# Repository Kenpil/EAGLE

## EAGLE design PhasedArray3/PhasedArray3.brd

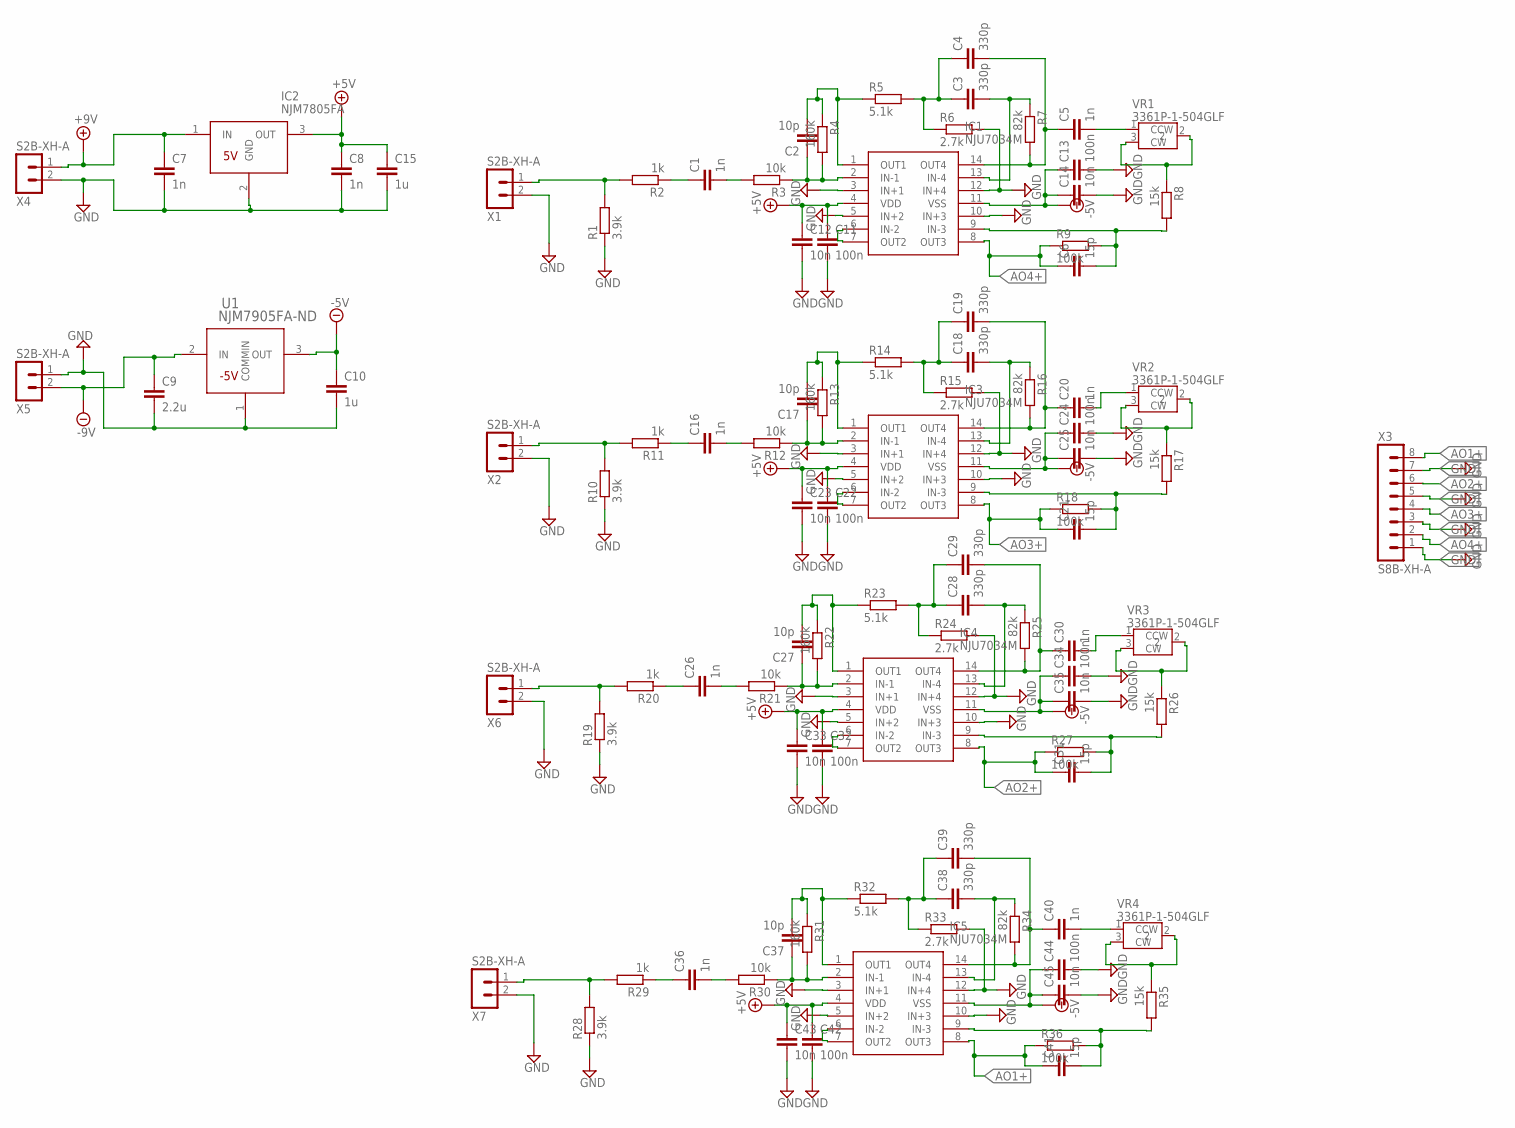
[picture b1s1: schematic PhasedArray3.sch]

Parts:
C1, C5, C7, C8, C16, C20, C26, C30, C36, C40: 1n; C0603K
C2, C17, C27, C37: 10p; C0603K
C3, C4, C18, C19, C28, C29, C38, C39: 330p; C0603K
C6, C21, C31, C41: 15p; C0603K
C9: 2.2u; C0805K
C10, C15: 1u; C0805K
C11, C13, C22, C24, C32, C34, C42, C44: 100n; C0603K
C12, C14, C23, C25, C33, C35, C43, C45: 10n; C0603K
IC1, IC3, IC4, IC5: NJU7034M; SOIC127P680X175-14N
IC2: NJM7805FA; TO254P500X1000X2170-3P
R1, R10, R19, R28: 3.9k; R0603
R2, R11, R20, R29: 1k; R0603
R3, R12, R21, R30: 10k; R0603
R4, R13, R22, R31: 160k; R0603
R5, R14, R23, R32: 5.1k; R0603
R6, R15, R24, R33: 2.7k; R0603
R7, R16, R25, R34: 82k; R0603
R8, R17, R26, R35: 15k; R0603
R9, R18, R27, R36: 100k; R0603
U1: NJM7905FA-ND; NJR-TO-220F-3_NJR
VR1, VR2, VR3, VR4: 3361P-1-504GLF; 3361P1253GLF
X1, X2, X4, X5, X6, X7: S2B-XH-A
X3: S8B-XH-A

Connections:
+5V: C8.1, C11.1, C12.1, C15.1, C22.1, C23.1, C32.1, C33.1, C42.1, C43.1, IC1.4 (VDD), IC2.3 (OUT), IC3.4 (VDD), IC4.4 (VDD), IC5.4 (VDD)
+9V: C7.1, IC2.1 (IN), X4.1
-5V: C10.1, C13.1, C14.1, C24.1, C25.1, C34.1, C35.1, C44.1, C45.1, IC1.11 (VSS), IC3.11 (VSS), IC4.11 (VSS), IC5.11 (VSS), U1.3 (OUT)
-9V: C9.1, U1.2 (IN), X5.2
AO1+: C41.1, IC5.8 (OUT3), R36.1, X3.8
AO2+: C31.1, IC4.8 (OUT3), R27.1, X3.6
AO3+: C21.1, IC3.8 (OUT3), R18.1, X3.4
AO4+: C6.1, IC1.8 (OUT3), R9.1, X3.2
GND: C7.2, C8.2, C9.2, C10.2, C11.2, C12.2, C13.2, C14.2, C15.2, C22.2, C23.2, C24.2, C25.2, C32.2, C33.2, C34.2, C35.2, C42.2, C43.2, C44.2, C45.2, IC1.3 (IN+1), IC1.5 (IN+2), IC1.10 (IN+3), IC1.12 (IN+4), IC2.2 (GND), IC3.3 (IN+1), IC3.5 (IN+2), IC3.10 (IN+3), IC3.12 (IN+4), IC4.3 (IN+1), IC4.5 (IN+2), IC4.10 (IN+3), IC4.12 (IN+4), IC5.3 (IN+1), IC5.5 (IN+2), IC5.10 (IN+3), IC5.12 (IN+4), R1.1, R6.2, R10.1, R15.2, R19.1, R24.2, R28.1, R33.2, U1.1 (COMMIN), X1.2, X2.2, X3.1, X3.3, X3.5, X3.7, X4.2, X5.1, X6.2, X7.2
unnamed: R1.2, R2.2, X1.1
unnamed: C1.1, R2.1
unnamed: C2.2, IC1.1 (OUT1), R4.1, R5.1
unnamed: C1.2, R3.2
unnamed: C2.1, IC1.2 (IN-1), R3.1, R4.2
unnamed: C3.1, C4.1, R5.2, R6.1
unnamed: C4.2, C5.1, IC1.14 (OUT4), R7.2
unnamed: C3.2, IC1.13 (IN-4), R7.1
unnamed: C5.2, VR1.1 (CCW)
unnamed: C6.2, IC1.9 (IN-3), R8.2, R9.2
unnamed: R8.1, VR1.2, VR1.3 (CW)
unnamed: IC1.6 (IN-2), IC1.7 (OUT2)
unnamed: R10.2, R11.2, X2.1
unnamed: C16.1, R11.1
unnamed: C16.2, R12.2
unnamed: C17.1, IC3.2 (IN-1), R12.1, R13.2
unnamed: C17.2, IC3.1 (OUT1), R13.1, R14.1
unnamed: C18.1, C19.1, R14.2, R15.1
unnamed: C18.2, IC3.13 (IN-4), R16.1
unnamed: C19.2, C20.1, IC3.14 (OUT4), R16.2
unnamed: C21.2, IC3.9 (IN-3), R17.2, R18.2
unnamed: C20.2, VR2.1 (CCW)
unnamed: R17.1, VR2.2, VR2.3 (CW)
unnamed: IC3.6 (IN-2), IC3.7 (OUT2)
unnamed: R19.2, R20.2, X6.1
unnamed: C26.1, R20.1
unnamed: C26.2, R21.2
unnamed: C27.1, IC4.2 (IN-1), R21.1, R22.2
unnamed: C27.2, IC4.1 (OUT1), R22.1, R23.1
unnamed: C28.1, C29.1, R23.2, R24.1
unnamed: C28.2, IC4.13 (IN-4), R25.1
unnamed: C29.2, C30.1, IC4.14 (OUT4), R25.2
unnamed: C31.2, IC4.9 (IN-3), R26.2, R27.2
unnamed: C30.2, VR3.1 (CCW)
unnamed: R26.1, VR3.2, VR3.3 (CW)
unnamed: IC4.6 (IN-2), IC4.7 (OUT2)
unnamed: R28.2, R29.2, X7.1
unnamed: C36.1, R29.1
unnamed: C36.2, R30.2
unnamed: C37.1, IC5.2 (IN-1), R30.1, R31.2
unnamed: C37.2, IC5.1 (OUT1), R31.1, R32.1
unnamed: C38.1, C39.1, R32.2, R33.1
unnamed: C38.2, IC5.13 (IN-4), R34.1
unnamed: C39.2, C40.1, IC5.14 (OUT4), R34.2
unnamed: C41.2, IC5.9 (IN-3), R35.2, R36.2
unnamed: C40.2, VR4.1 (CCW)
unnamed: R35.1, VR4.2, VR4.3 (CW)
unnamed: IC5.6 (IN-2), IC5.7 (OUT2)

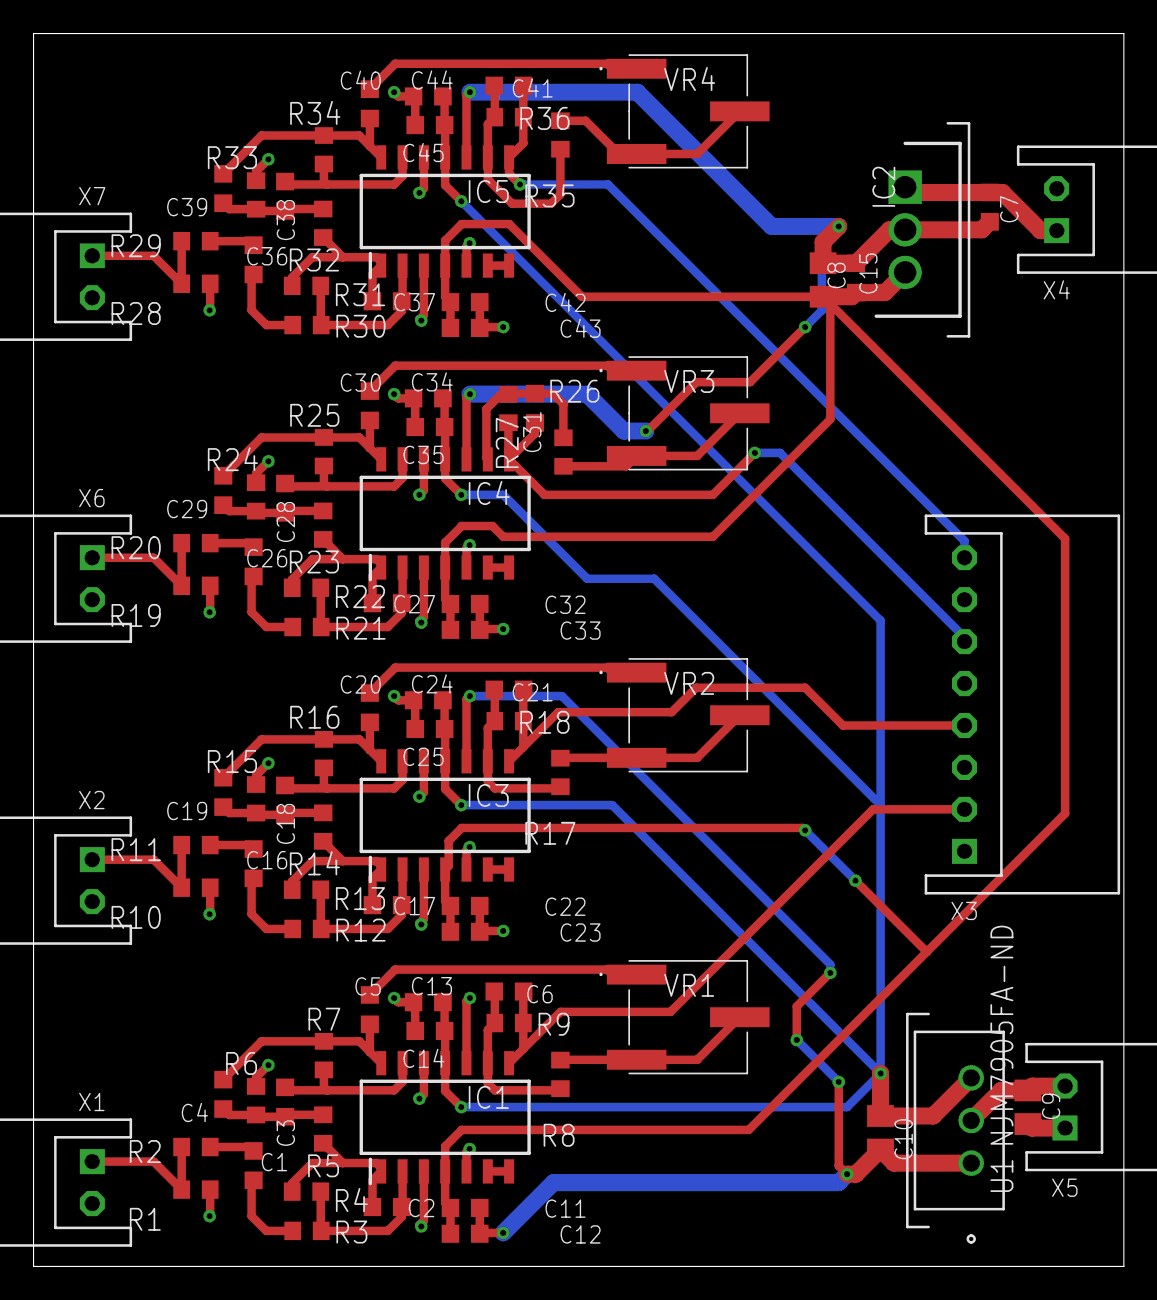
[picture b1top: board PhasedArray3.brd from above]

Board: 2 copper layers, 65.0 x 73.5 mm, 98 parts (0 on the bottom side), 57 nets.

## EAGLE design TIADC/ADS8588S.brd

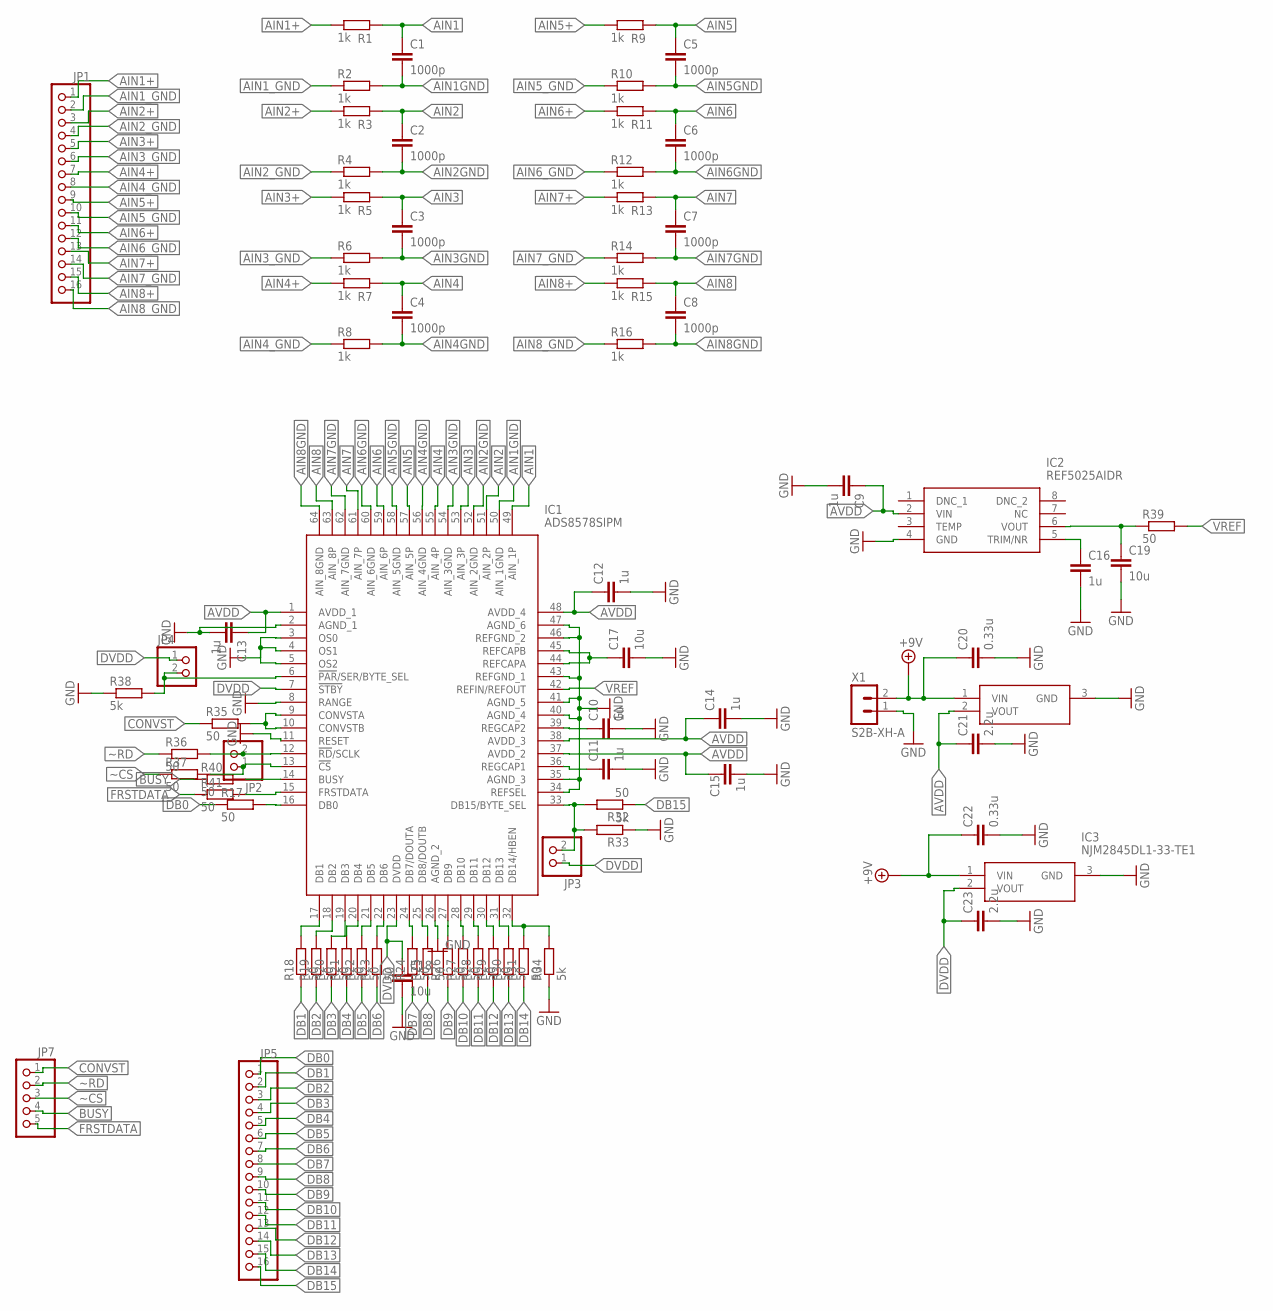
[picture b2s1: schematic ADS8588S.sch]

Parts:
C1, C2, C3, C4, C5, C6, C7, C8: 1000p; C0603K
C9, C10, C11, C12, C13, C14, C15, C16: 1u; C0603K
C17, C18, C19: 10u; C0805K
C20, C22: 0.33u; C0603K
C21, C23: 2.2u; C0805K
IC1: ADS8578SIPM; QFP50P1200X1200X160-64N
IC2: REF5025AIDR; SOIC127P600X175-8N
IC3: NJM2845DL1-33-TE1; TO-252-3-L1
IC5: NJM2845DL1-05-TE1; TO-252-3-L1
JP1, JP5: PINHD-1X16; 1X16
JP2, JP3, JP4: PINHD-1X2; 1X02
JP7: PINHD-1X5; 1X05
R1, R2, R3, R4, R5, R6, R7, R8, R9, R10, R11, R12, R13, R14, R15, R16: 1k; R0603
R17, R18, R19, R20, R21, R22, R23, R24, R25, R26, R27, R28, R29, R30, R31, R32, R35, R36, R37, R39, R40, R41: 50; R0603
R33, R34, R38: 5k; R0603
X1: S2B-XH-A

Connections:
AIN1: C1.1, IC1.49 (AIN_1P), R1.2
AIN1+: JP1.1, R1.1
AIN1GND: C1.2, IC1.50 (AIN_1GND), R2.2
AIN1_GND: JP1.2, R2.1
AIN2: C2.1, IC1.51 (AIN_2P), R3.2
AIN2+: JP1.3, R3.1
AIN2GND: C2.2, IC1.52 (AIN_2GND), R4.2
AIN2_GND: JP1.4, R4.1
AIN3: C3.1, IC1.53 (AIN_3P), R5.2
AIN3+: JP1.5, R5.1
AIN3GND: C3.2, IC1.54 (AIN_3GND), R6.2
AIN3_GND: JP1.6, R6.1
AIN4: C4.1, IC1.55 (AIN_4P), R7.2
AIN4+: JP1.7, R7.1
AIN4GND: C4.2, IC1.56 (AIN_4GND), R8.2
AIN4_GND: JP1.8, R8.1
AIN5: C5.1, IC1.57 (AIN_5P), R9.2
AIN5+: JP1.9, R9.1
AIN5GND: C5.2, IC1.58 (AIN_5GND), R10.2
AIN5_GND: JP1.10, R10.1
AIN6: C6.1, IC1.59 (AIN_6P), R11.2
AIN6+: JP1.11, R11.1
AIN6GND: C6.2, IC1.60 (AIN_6GND), R12.2
AIN6_GND: JP1.12, R12.1
AIN7: C7.1, IC1.61 (AIN_7P), R13.2
AIN7+: JP1.13, R13.1
AIN7GND: C7.2, IC1.62 (AIN_7GND), R14.2
AIN7_GND: JP1.14, R14.1
AIN8: C8.1, IC1.63 (AIN_8P), R15.2
AIN8+: JP1.15, R15.1
AIN8GND: C8.2, IC1.64 (AIN_8GND), R16.2
AIN8_GND: JP1.16, R16.1
AVDD: C9.1, C12.1, C13.1, C14.1, C15.1, C21.1, IC1.1 (AVDD_1), IC1.37 (AVDD_2), IC1.38 (AVDD_3), IC1.48 (AVDD_4), IC2.2 (VIN), IC5.2 (VOUT)
BUSY: JP7.4, R40.1
CONVST: JP7.1, R35.1
DB0: JP5.1, R17.1
DB1: JP5.2, R18.1
DB2: JP5.3, R19.1
DB3: JP5.4, R20.1
DB4: JP5.5, R21.1
DB5: JP5.6, R22.1
DB6: JP5.7, R23.1
DB7: JP5.8, R24.1
DB8: JP5.9, R25.1
DB9: JP5.10, R26.1
DB10: JP5.11, R27.1
DB11: JP5.12, R28.1
DB12: JP5.13, R29.1
DB13: JP5.14, R30.1
DB14: JP5.15, R31.1
DB15: JP5.16, R32.1
DVDD: C18.1, C23.1, IC1.7 (!STBY), IC1.23 (DVDD), IC3.2 (VOUT), JP3.1, JP4.1
DVDD1: C19.1, IC2.6 (VOUT), R39.1
FRSTDATA: JP7.5, R41.1
unnamed: C17.1, IC1.44 (REFCAPA), IC1.45 (REFCAPB)
unnamed: IC1.9 (CONVSTA), IC1.10 (CONVSTB), R35.2
unnamed: C10.1, IC1.39 (REGCAP2)
unnamed: C11.1, IC1.36 (REGCAP1)
unnamed: IC1.17 (DB1), R18.2
unnamed: IC1.18 (DB2), R19.2
unnamed: IC1.19 (DB3), R20.2
unnamed: IC1.20 (DB4), R21.2
unnamed: IC1.21 (DB5), R22.2
unnamed: IC1.22 (DB6), R23.2
unnamed: IC1.24 (DB7/DOUTA), R24.2
unnamed: IC1.25 (DB8/DOUTB), R25.2
unnamed: IC1.27 (DB9), R26.2
unnamed: IC1.28 (DB10), R27.2
unnamed: IC1.29 (DB11), R28.2
unnamed: IC1.30 (DB12), R29.2
unnamed: IC1.31 (DB13), R30.2
unnamed: IC1.32 (DB14/HBEN), R31.2, R34.2
unnamed: IC1.33 (DB15/BYTE_SEL), JP3.2, R32.2, R33.2
unnamed: IC1.16 (DB0), R17.2
unnamed: IC1.6 (!PAR!/SER/BYTE_SEL), JP4.2, R38.2
unnamed: C16.1, IC2.5 (TRIM/NR)
unnamed: IC1.12 (!RD!/SCLK), JP2.2, R36.2
unnamed: IC1.13 (!CS), JP2.1, R37.2
unnamed: IC1.15 (FRSTDATA), R41.2
unnamed: IC1.14 (BUSY), R40.2
VREF: IC1.42 (REFIN/REFOUT), R39.2
~CS: JP7.3, R37.1
~RD: JP7.2, R36.1

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
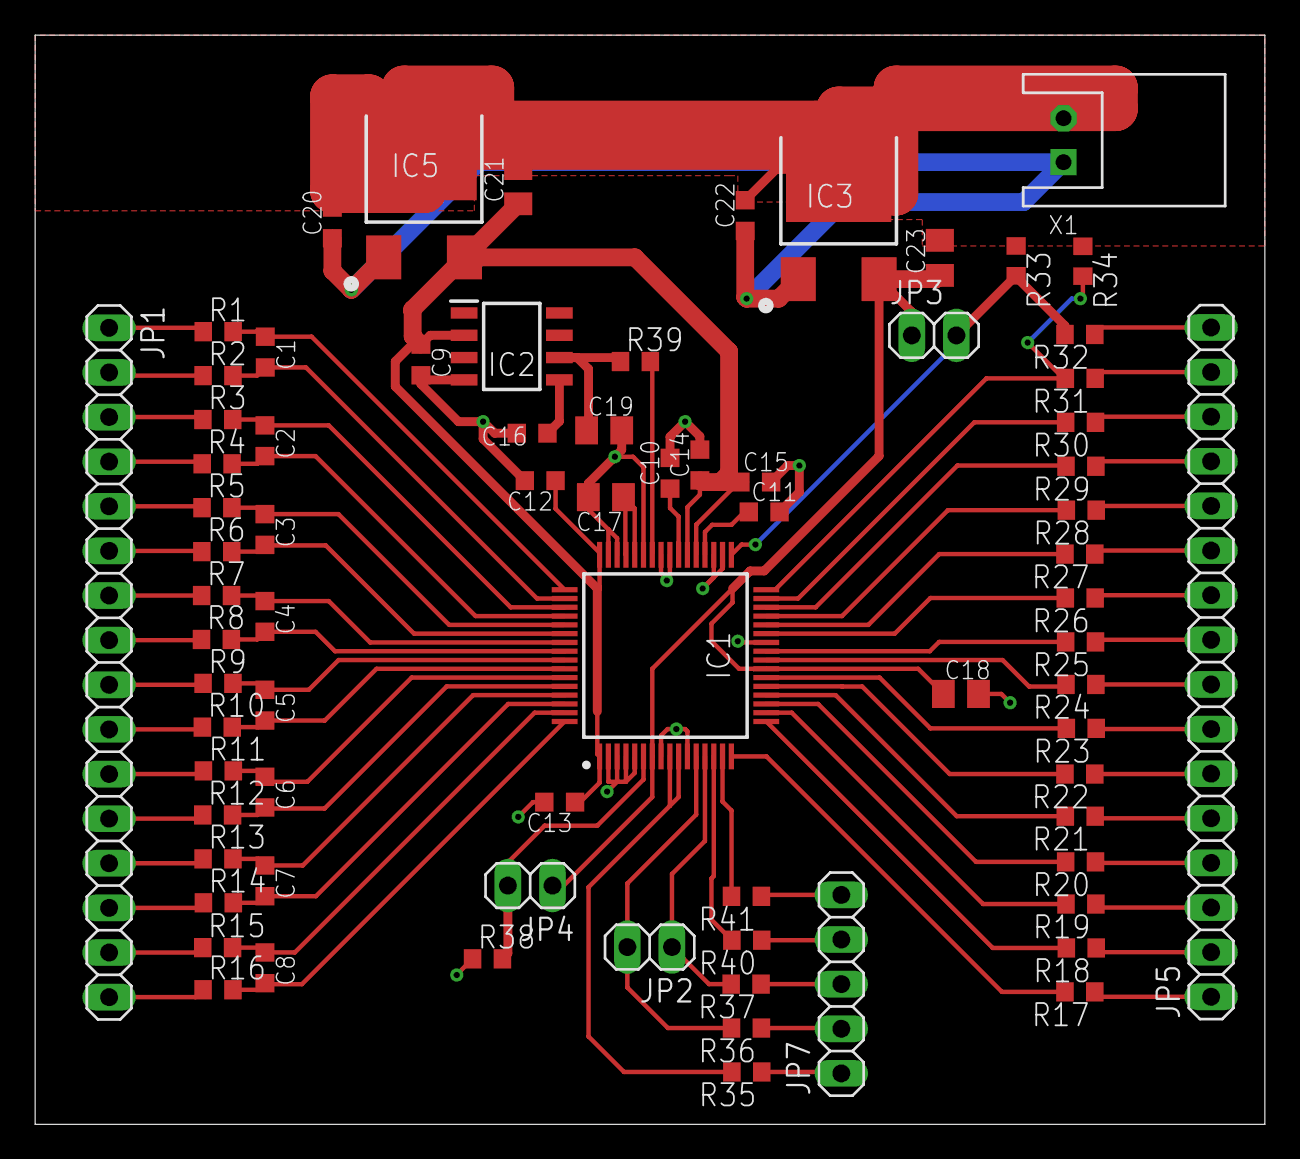
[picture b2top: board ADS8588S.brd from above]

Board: 2 copper layers, 70.0 x 62.0 mm, 75 parts (0 on the bottom side), 85 nets.

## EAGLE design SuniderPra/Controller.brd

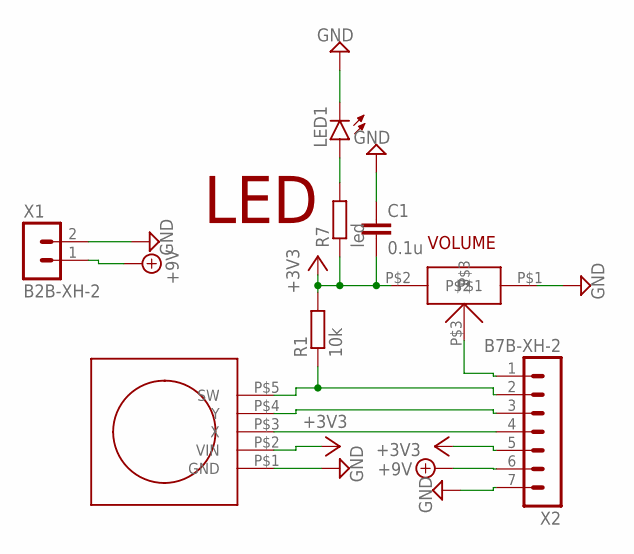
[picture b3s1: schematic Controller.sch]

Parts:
C1: 0.1u; C050-024X044
JOY1: JOY
LED1: LED3MM
POT1: POTENTIOMETER
R1: 10k; 0207/7
R7: led; 0207/7
X1: B2B-XH-2; B2B-XH-A
X2: B7B-XH-2; B7B-XH-A

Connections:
+3V3: C1.2, JOY1.P$2 (VIN), POT1.P$2, R1.2, R7.1, X2.5
+9V: X1.1, X2.6
GND: C1.1, JOY1.P$1 (GND), LED1.K (C), POT1.P$1, X1.2, X2.7
unnamed: JOY1.P$4 (Y), X2.3
unnamed: JOY1.P$5 (SW), R1.1, X2.2
unnamed: POT1.P$3, X2.1
unnamed: JOY1.P$3 (X), X2.4
unnamed: LED1.A, R7.2

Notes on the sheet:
VOLUME
LED

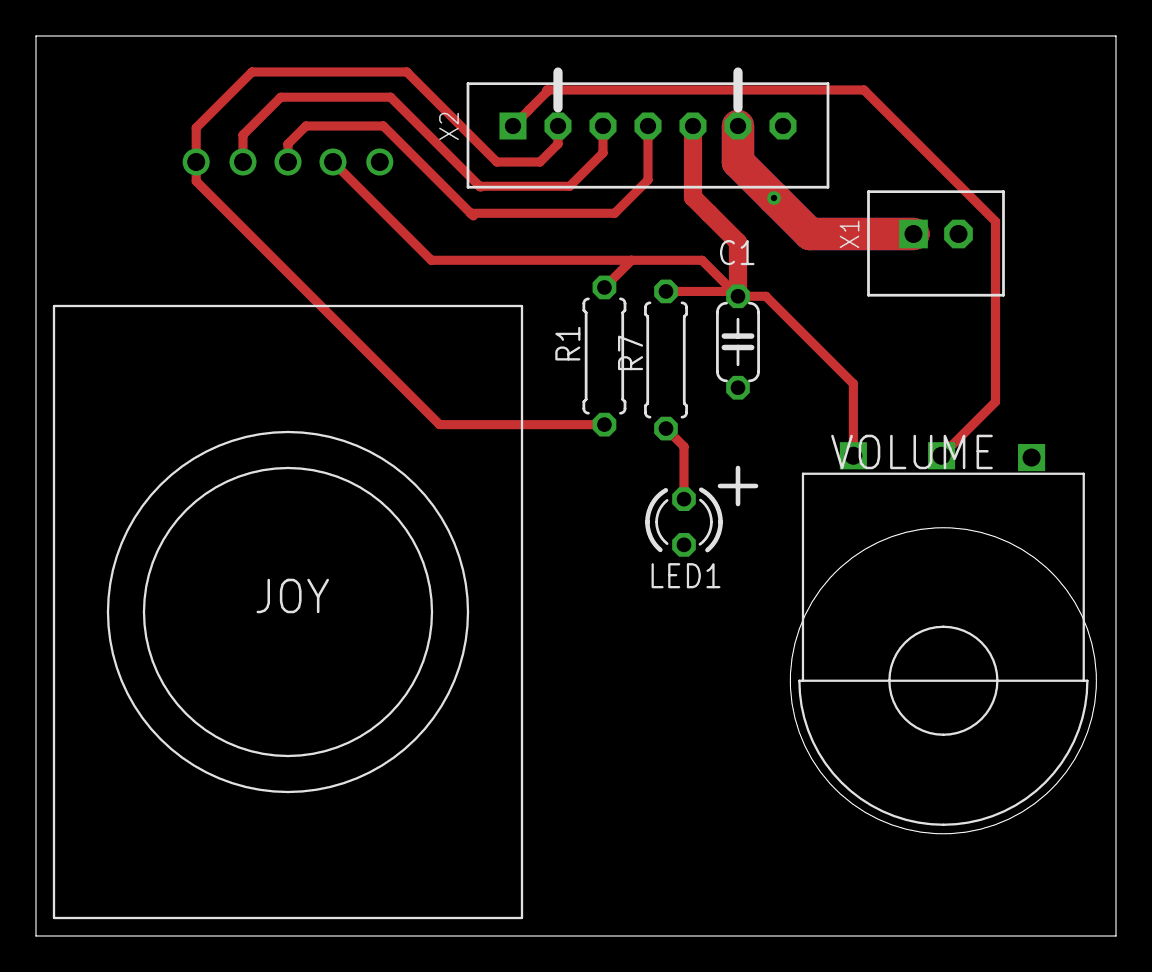
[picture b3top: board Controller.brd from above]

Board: 2 copper layers, 60.0 x 50.0 mm, 8 parts (0 on the bottom side), 8 nets.

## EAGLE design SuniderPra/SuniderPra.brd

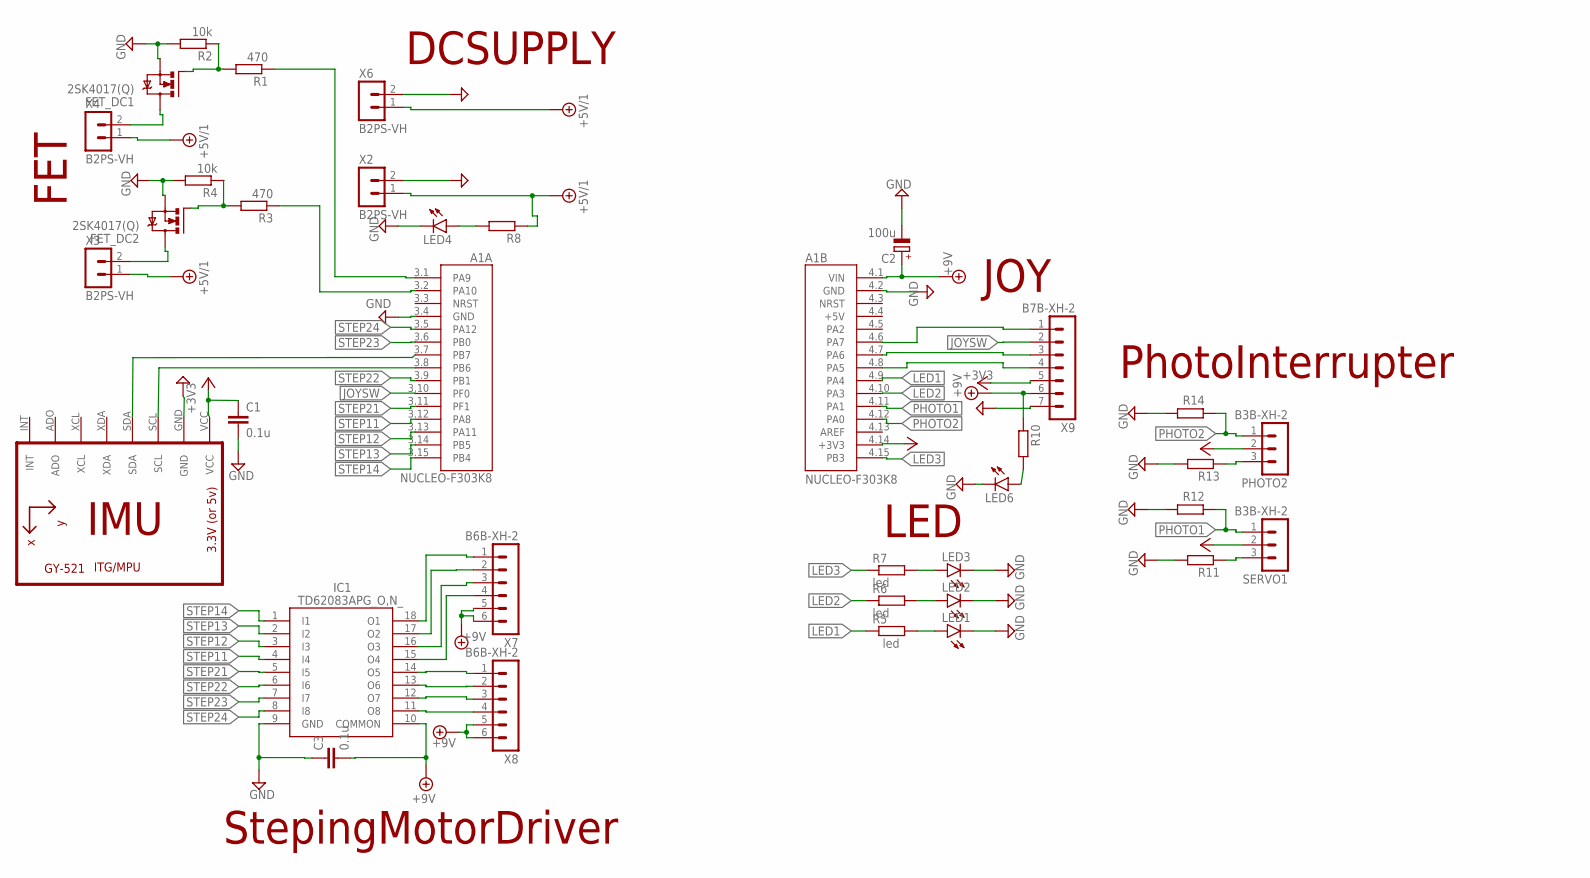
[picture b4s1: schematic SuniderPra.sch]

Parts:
A1: NUCLEO-F303K8; MODULE_NUCLEO-F303K8
C1, C3: 0.1u; C050-024X044
C2: 100u; E2,5-6E
FET_DC1, FET_DC2: 2SK4017(Q); TO230P230X650X740-3P
IC1: TD62083APG_O,N_; DIP762W60P254L2510H445Q18N
IMU: GY-521MPU6050; GY-521
LED1, LED2, LED3, LED4, LED6: LED3MM
PHOTO2: B3B-XH-2; B3B-XH-A
R1, R3: 470; 0207/7
R2, R4, R12, R14: 10k; 0207/7
R5, R6, R7, R8, R10: led; 0207/7
R11, R13: 220; 0207/7
SERVO1: B3B-XH-2; B3B-XH-A
X2, X3, X4, X6: B2PS-VH
X7, X8: B6B-XH-2; B6B-XH-A
X9: B7B-XH-2; B7B-XH-A

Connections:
+3V3: A1.4.14 (+3V3), C1.1, IMU.VCC, PHOTO2.2, SERVO1.2, X9.5
+5V/1: R8.1, X2.1, X3.1, X4.1, X6.1
+9V: A1.4.1 (VIN), C2.+, C3.2, IC1.10 (COMMON), R10.1, X7.5, X7.6, X8.5, X8.6, X9.6
GND: A1.3.4 (GND), A1.4.2 (GND), C1.2, C2.-, C3.1, FET_DC1.3 (S), FET_DC2.3 (S), IC1.9 (GND), IMU.GND, LED1.K (C), LED2.K (C), LED3.K (C), LED4.K (C), LED6.K (C), R2.2, R4.2, R11.2, R12.2, R13.2, R14.2, X2.2, X6.2, X9.7
JOYSW: A1.3.10 (PF0), X9.2
LED1: A1.4.9 (PA4), R5.1
LED2: A1.4.10 (PA3), R6.1
LED3: A1.4.15 (PB3), R7.1
unnamed: A1.3.8 (PB6), IMU.SCL
unnamed: A1.3.7 (PB7), IMU.SDA
unnamed: IC1.18 (O1), X7.1
unnamed: IC1.12 (O7), X8.3
unnamed: A1.4.8 (PA5), X9.4
unnamed: FET_DC1.1 (G), R1.2, R2.1
unnamed: FET_DC2.2 (D), X3.2
unnamed: A1.3.2 (PA10), R3.1
unnamed: FET_DC2.1 (G), R3.2, R4.1
unnamed: FET_DC1.2 (D), X4.2
unnamed: LED2.A, R6.2
unnamed: IC1.13 (O6), X8.2
unnamed: A1.3.1 (PA9), R1.1
unnamed: LED1.A, R5.2
unnamed: LED3.A, R7.2
unnamed: IC1.14 (O5), X8.1
unnamed: IC1.15 (O4), X7.4
unnamed: A1.4.6 (PA7), X9.1
unnamed: A1.4.7 (PA6), X9.3
unnamed: LED4.A, R8.2
unnamed: IC1.16 (O3), X7.3
unnamed: IC1.17 (O2), X7.2
unnamed: LED6.A, R10.2
unnamed: PHOTO2.3, R13.1
unnamed: R11.1, SERVO1.3
unnamed: IC1.11 (O8), X8.4
PHOTO1: A1.4.11 (PA1), R12.1, SERVO1.1
PHOTO2: A1.4.12 (PA0), PHOTO2.1, R14.1
STEP11: A1.3.12 (PA8), IC1.4 (I4)
STEP12: A1.3.13 (PA11), IC1.3 (I3)
STEP13: A1.3.14 (PB5), IC1.2 (I2)
STEP14: A1.3.15 (PB4), IC1.1 (I1)
STEP21: A1.3.11 (PF1), IC1.5 (I5)
STEP22: A1.3.9 (PB1), IC1.6 (I6)
STEP23: A1.3.6 (PB0), IC1.7 (I7)
STEP24: A1.3.5 (PA12), IC1.8 (I8)

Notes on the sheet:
IMU
FET
LED
JOY
DCSUPPLY
StepingMotorDriver
PhotoInterrupter

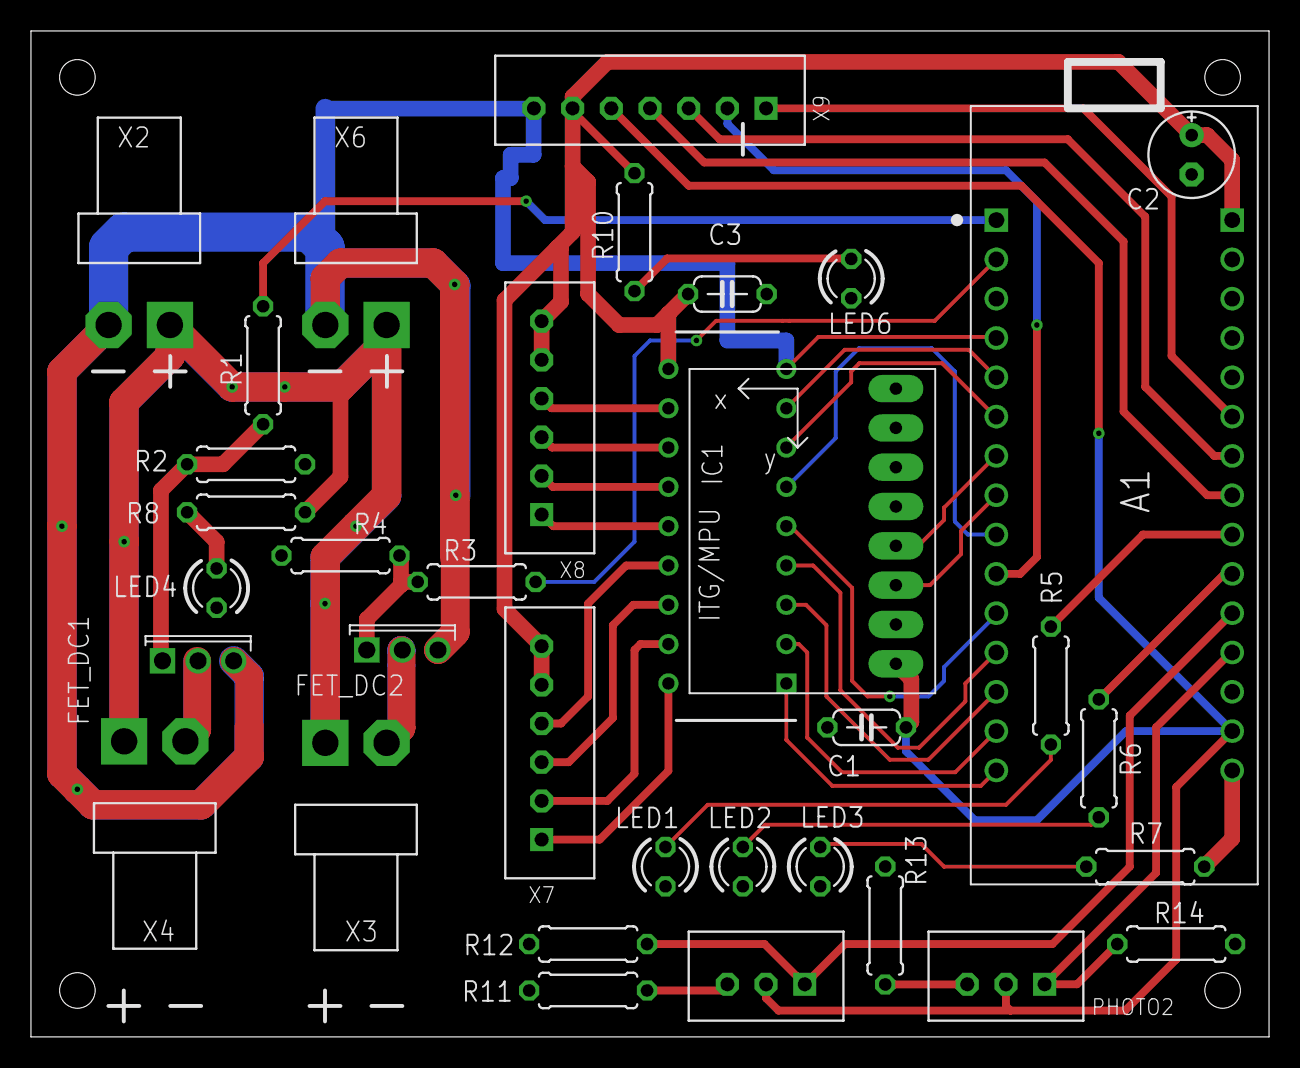
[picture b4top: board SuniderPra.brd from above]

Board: 2 copper layers, 80.0 x 65.0 mm, 35 parts (0 on the bottom side), 44 nets.
